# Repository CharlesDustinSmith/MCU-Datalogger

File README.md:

KiCad project

# MCU-Datalogger

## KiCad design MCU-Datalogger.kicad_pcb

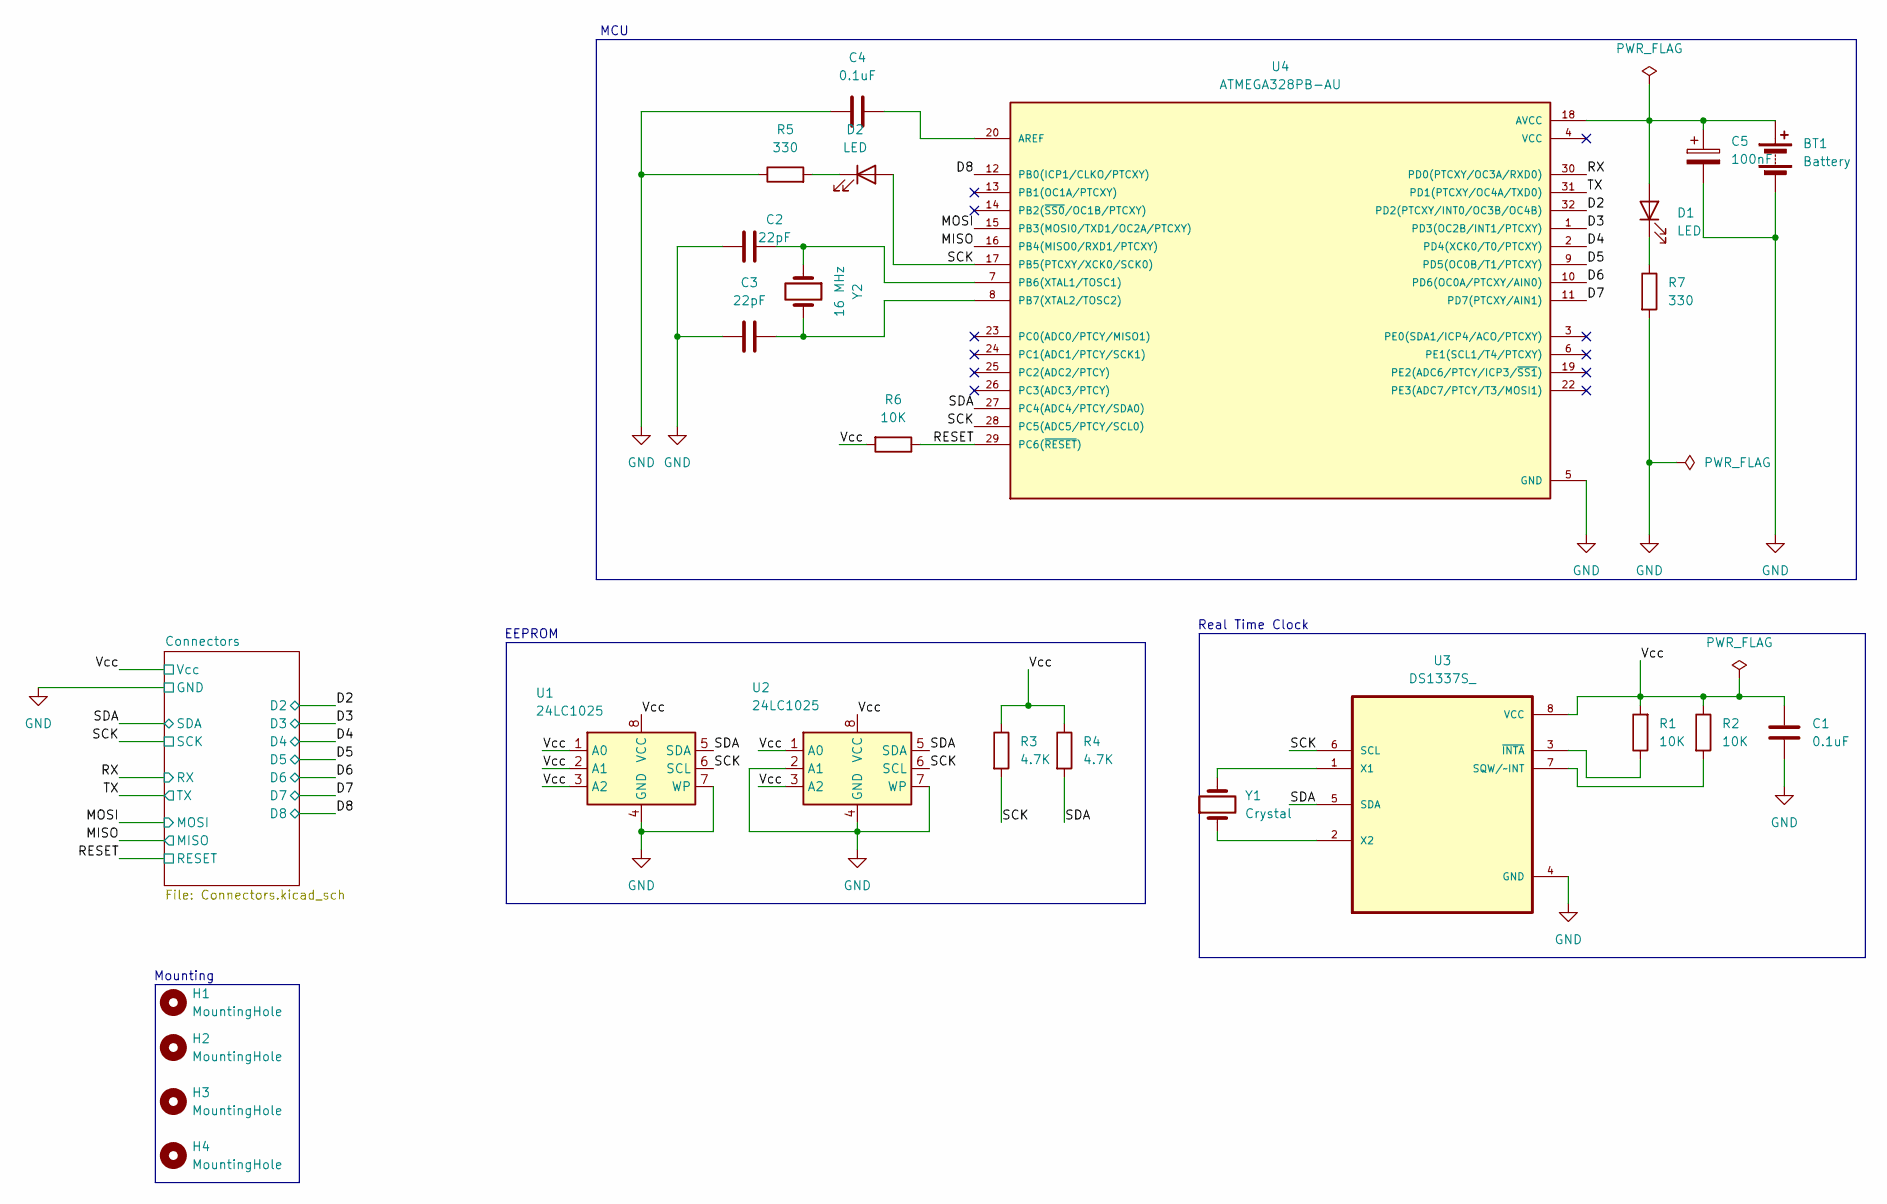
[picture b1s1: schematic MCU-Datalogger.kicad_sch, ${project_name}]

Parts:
BT1: Battery; PinHeader_1x02_P2.54mm_Vertical
C1, C4: 0.1uF; C_0805_2012Metric
C2, C3: 22pF; C_0805_2012Metric
C5: 100nF; C_0805_2012Metric
D1, D2: LED; LED_0805_2012Metric
H1, H2, H3, H4: MountingHole; MountingHole_2.1mm
R1, R2, R6: 10K; R_0805_2012Metric
R3, R4: 4.7K; R_0805_2012Metric
R5, R7: 330; R_0805_2012Metric
U1, U2: 24LC1025; SOIC-8_5.3x5.3mm_P1.27mm
U3: DS1337S_; SOIC127P600X175-8N
U4: ATMEGA328PB-AU; QFP80P900X900X120-32N
Y1: Crystal; Crystal_SMD_5032-2Pin_5.0x3.2mm_HandSoldering
Y2: 16 MHz; Crystal_SMD_5032-2Pin_5.0x3.2mm_HandSoldering

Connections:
/D2: U4.32 (PD2(PTCXY/INT0/OC3B/OC4B)); also elsewhere on the board
/D3: U4.1 (PD3(OC2B/INT1/PTCXY)); also elsewhere on the board
/D4: U4.2 (PD4(XCK0/T0/PTCXY)); also elsewhere on the board
/D5: U4.9 (PD5(OC0B/T1/PTCXY)); also elsewhere on the board
/D6: U4.10 (PD6(OC0A/PTCXY/AIN0)); also elsewhere on the board
/D7: U4.11 (PD7(PTCXY/AIN1)); also elsewhere on the board
/D8: U4.12 (PB0(ICP1/CLKO/PTCXY)); also elsewhere on the board
/MISO: U4.16 (PB4(MISO0/RXD1/PTCXY)); also elsewhere on the board
/MOSI: U4.15 (PB3(MOSI0/TXD1/OC2A/PTCXY)); also elsewhere on the board
/RESET: R6.1, U4.29 (PC6(~RESET)); also elsewhere on the board
/RX: U4.30 (PD0(PTCXY/OC3A/RXD0)); also elsewhere on the board
/SCK: D2.2 (A), R3.2, U1.6 (SCL), U2.6 (SCL), U3.6 (SCL), U4.17 (PB5(PTCXY/XCK0/SCK0)), U4.28 (PC5(ADC5/PTCY/SCL0)); also elsewhere on the board
/SDA: R4.2, U1.5 (SDA), U2.5 (SDA), U3.5 (SDA), U4.27 (PC4(ADC4/PTCY/SDA0)); also elsewhere on the board
/TX: U4.31 (PD1(PTCXY/OC4A/TXD0)); also elsewhere on the board
/Vcc: C1.1, R1.2, R2.1, R3.1, R4.1, R6.2, U1.1 (A0), U1.2 (A1), U1.3 (A2), U1.8 (VCC), U2.1 (A0), U2.3 (A2), U2.8 (VCC), U3.8 (VCC); also elsewhere on the board
GND: BT1.2 (-), C1.2, C2.1, C3.1, C4.1, C5.2, R5.1, R7.2, U1.4 (GND), U1.7 (WP), U2.2 (A1), U2.4 (GND), U2.7 (WP), U3.4 (GND), U4.5 (GND), U4.21 (GND); also elsewhere on the board
unnamed: BT1.1 (+), C5.1, D1.2 (A), U4.18 (AVCC)
unnamed: D1.1 (K), R7.1
unnamed: D2.1 (K), R5.2
unnamed: R2.2, U3.7 (SQW/~INT)
unnamed: U3.1 (X1), Y1.2
unnamed: U3.2 (X2), Y1.1
unnamed: R1.1, U3.3 (~INTA)
unnamed: C4.2, U4.20 (AREF)
unnamed: C2.2, U4.7 (PB6(XTAL1/TOSC1)), Y2.1
unnamed: C3.2, U4.8 (PB7(XTAL2/TOSC2)), Y2.2

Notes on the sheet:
Real Time Clock
MCU
Mounting
EEPROM

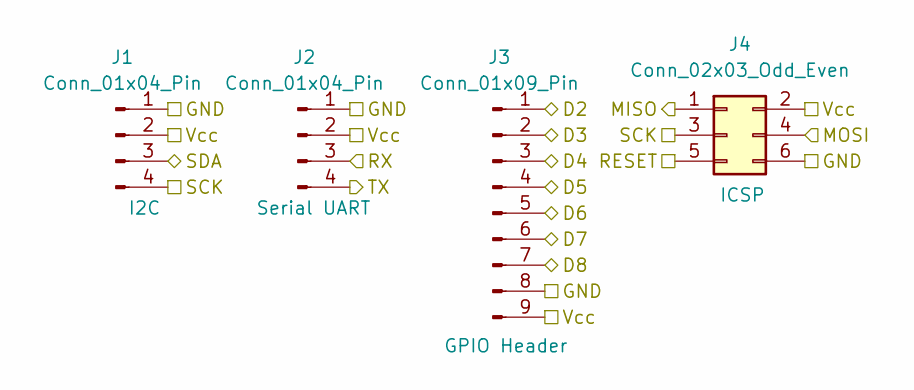
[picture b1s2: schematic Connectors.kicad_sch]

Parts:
J1, J2: Conn_01x04_Pin; PinHeader_1x04_P2.54mm_Vertical
J3: Conn_01x09_Pin; PinHeader_1x09_P2.54mm_Vertical_SMD_Pin1Left
J4: Conn_02x03_Odd_Even; PinHeader_2x03_P2.54mm_Vertical

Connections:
/D2: J3.1; also elsewhere on the board
/D3: J3.2; also elsewhere on the board
/D4: J3.3; also elsewhere on the board
/D5: J3.4; also elsewhere on the board
/D6: J3.5; also elsewhere on the board
/D7: J3.6; also elsewhere on the board
/D8: J3.7; also elsewhere on the board
/MISO: J4.1; also elsewhere on the board
/MOSI: J4.4; also elsewhere on the board
/RESET: J4.5; also elsewhere on the board
/RX: J2.3; also elsewhere on the board
/SCK: J1.4, J4.3; also elsewhere on the board
/SDA: J1.3; also elsewhere on the board
/TX: J2.4; also elsewhere on the board
/Vcc: J1.2, J2.2, J3.9, J4.2; also elsewhere on the board
GND: J1.1, J2.1, J3.8, J4.6; also elsewhere on the board

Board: 2 copper layers, 29 parts (0 on the bottom side), 26 nets, no tracks yet.

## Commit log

2025-12-15 Did a bit of clean up. Removed the MCU-Datalogger-backups & fp-info-cache
2025-12-15 Clean up
2025-12-15 deletes files attempt 2
2025-12-15 Added symbols into the schematics
2025-12-16 Wiring Completion
    Wiring completed and the symbols have been rearranged, the footprints were added for all of the symbols. Connector hierarchical sheet added to the project.
2025-12-16 Comments
    Completed the comments for the schematics
2025-12-16 Populate NewPCB
    Imported the schematic into newPCB. This made also add the 3D model for all of the components.
2025-12-16 Constraint
    Add edge cut to NewPCB drawing
